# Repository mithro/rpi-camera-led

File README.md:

# RPi Camera LED

An interposer for the Raspberry Pi camera flex cable (15 pin, 1.0 mm pitch FPC).
It connects the Pi and camera, passes the camera bus through, and adds a
CH32V003A4M6 for I2C-controlled GPIO 11/12, PWM illumination LEDs, and ambient
light sensing. GPIO 11/12 use 10 kOhm couplers so the MCU can sense Pi-side
levels or drive the camera-side signals.

## Hardware

[KiCad schematic](hardware/rpi-camera-led.kicad_sch) ·
[PDF](hardware/rpi-camera-led.pdf) ·
[board](hardware/rpi-camera-led.kicad_pcb)

### Board: 15-way FFC camera interposer

| 3D render, top | 3D render, bottom | Layout (copper, silk, outline) |
|:--------------:|:-----------------:|:------------------------------:|
|  |  |  |

The routed interposer is 46.0 × 43.0 mm, two layers, with components on both
sides. J1 faces the Raspberry Pi and J2 faces the camera; they are opposite
edge-mounted so the two cable segments leave in line. The 11 mm lens aperture
is centered on the intended camera optical axis, and the illumination LEDs sit
around the aperture on the target-facing side. A fit-check using the supplied
Raspberry Pi Camera v3 3MF model guided the redesign: the 11 mm lens aperture
is aligned to the model's optical axis, and the four interposer holes now
match its 20.0 × 12.5 mm mounting pattern. The model's hole-pattern center is
offset 6.25 mm from the optical axis, so the holes are intentionally
asymmetric about the aperture. The LED row was moved clear of the relocated
mounting holes.

The four 2.2 mm mounting holes follow the supplied Raspberry Pi Camera v3
3MF mesh; see [hardware/cad/README.md](hardware/cad/README.md) for the model
datum and conversion details. The wider outline clears the connectors while
allowing the interposer to mount over the camera; the 6.05 mm-radius two-layer
copper keepout around the lens opening preserves copper-to-aperture edge
clearance. `check_pcb.py` asserts connector alignment and the camera-model
hole coordinates, pitch, and drill.
The 4-pin Qwiic/JST-SH connector (J3) is also edge-facing, with its cable entry
at the lower board edge (J3 at x=17.5 mm, y=53.7 mm, rotated 180°) so the plug
can be inserted without obstructing the camera or its flex. `check_pcb.py`
asserts this edge orientation and the J3 pad map as well as the FFC alignment.

**Routing and design checks pass:** KiCad DRC reports zero violations and
zero unconnected items, schematic ERC is clean, and the netlist matches the
design checker. The three camera differential pairs have these PCB-track
lengths (pads/connectors excluded):

| Pair | P length | N length | Intra-pair mismatch |
|---|---:|---:|---:|
| CSI data 0 | 35.5720 mm | 35.0432 mm | 0.5288 mm |
| CSI data 1 | 35.8428 mm | 35.3092 mm | 0.5336 mm |
| CSI clock | 36.9758 mm | 38.2571 mm | 1.2813 mm |

The data-pair averages are 2.3089 mm and 2.0405 mm shorter than the clock-pair
average. At a rough FR-4 propagation estimate of 6–7 ps/mm, those differences
correspond to about 12–16 ps; this is not a MIPI compliance claim. The actual
stackup/impedance and camera/host timing budget have not been verified.
Confirm the chosen fabricator's stackup and electrical rules before calling
the interposer signal-integrity qualified.

The Gerber/drill, position, sourced BOM and DRC archive is generated by
`uv run hardware/tools/export_manufacturing.py` into
`tmp/manufacturing/manufacturing.zip`. Export is blocked by any DRC errors or
unconnected items. The package is complete for review; verify vendor-specific
rules, current component availability, and the physical camera/FFC fit before
ordering. Production board identity/revision and license/attribution silkscreen
still need to be added and audited.

The camera/interposer stack model and test-render instructions are in
[hardware/cad/README.md](hardware/cad/README.md). The supplied camera model is
included as a faceted STEP converted from its 3MF source; the Raspberry Pi FFC
path remains illustrative.

| Populated interposer | Camera/interposer stackup concept |
|:--------------------:|:---------------------------------:|
|  |  |

The fit-check image shows the routed board with the supplied model's optical
axis and all four mounting holes aligned. This is a model-based fit check, not
physical verification; confirm the camera revision and mounting dimensions
before fabrication.

### How the cables run

| With cables fitted | Isometric |
|:------------------:|:---------:|
|  |  |

Both cables enter from the **outside** edges and run away from the board in
opposite directions, so the interposer drops into an existing cable run in
line. That follows from where the cable entry is on this connector: the
manufacturer's Section A‑A shows the solder tail stepping down and out at one
end while the cable channel opens at the other, and the top view labels
*Terminal* at one end and *Latch* at the other with the 5.30 mm housing
between them. It is also the only way a slide lock can work — you pull the
slider, insert the cable and push it back, all at the same end. So the cable
entry is at the latch end, away from the pads, and with each connector's
housing flush against its board edge that entry points outward.

The two cable stubs are drawn different ways up, and that is the point. J1 is
bottom contact, so its cable presents bared copper *downwards* and shows you
the blue backing; J2 is top contact, so its cable is the other way up and
shows you the conductors. That flip is the whole reason for pairing an F part
with an E part, and it is what lets both segments be ordinary Raspberry Pi
camera cables — the same flip you can see in a real cable, blue stiffener on
one face at one end, bared conductors on the other face at the other.

The stubs are illustrative and are not part of the board: they exist only in a
throwaway copy that the render script builds and deletes. Their 16.00 × 0.30 mm
section is the drawing's recommended FFC dimension. The bared conductors and
the backing are drawn a little longer than the 4 mm insertion depth so that a
few millimetres of each stay visible outside the connector — otherwise the
orientation they exist to show would be buried inside it.

Regenerate the images with `uv run hardware/tools/render_board.py`, and the
connector models with `uv run hardware/tools/gen_connector_model.py`. The
render script refills the copper zones first, via the pcbnew Python module
inside the KiCad snap, because `kicad-cli` has no zone-fill command and a
stale pour renders as authoritatively as a fresh one — when this was first
wired up the stored B.Cu pour was less than half its true area, and refilling
it dropped DRC from 116 violations to 17.

### Connectors, and which cables fit

J1 and J2 are **not** the same part, and that is deliberate:

| | part | contacts | mates with |
|---|---|---|---|
| **J1** → Raspberry Pi | JUSHUO AFA07-S15**F**CA-00 (LCSC C262721) | **bottom** — cable copper faces the board | a standard Pi camera cable |
| **J2** → camera | JUSHUO AFA07-S15**E**CA-00 (LCSC C262742) | **top** — cable copper faces away | a standard Pi camera cable |

The reason is cable parity. A Raspberry Pi camera cable is an *opposite-side*
FFC — "type 2", contacts on one face at one end and the other face at the other
— because the Pi's CSI socket is top-contact and the camera module's is
bottom-contact. Cutting one continuous cable anywhere yields one same-side half
and one opposite-side half, so an interposer whose two connectors want the
copper on the *same* face forces one odd, hard-to-buy cable. One that wants it
on *opposite* faces absorbs the asymmetry, and both segments become ordinary
Raspberry Pi camera cables. Bottom-contact at J1 plus top-contact at J2 is that
pairing.

The two variants share one land pattern — verified against both JUSHUO drawings
— so nothing on the board moves between them. Since only the contact side
differs, and it is invisible on an assembled board, the distinction is called
out in each symbol's value, in the MPN, and as a `BOTTOM CONTACT` / `TOP
CONTACT` marker on the fab layer.

Both footprints and their 3D models live in this repository, in
`hardware/rpi-camera-led.pretty` and `hardware/rpi-camera-led.3dshapes`. KiCad's
stock footprint references a STEP file for the JUSHUO AFA07 series that does not
exist — not in the KiCad distribution and not in `kicad-packages3D` upstream,
which ships no JUSHUO models at all. Third-party libraries have one, but under
terms that forbid redistribution, so `hardware/tools/gen_connector_model.py`
builds it from the manufacturer's published drawing instead: a 22.00 × 6.95 ×
2.50 mm envelope matching the drawing's DIM D, the F.Fab outline and the side
view's height, with the housing and latch coloured as the drawing's notes
specify. Both STEP and WRL are generated, the latter in the 0.1-inch units
KiCad expects.

The direct pass-through signals are wired J1 pin *k* ↔ J2 pin *16−k*. That
looks reversed but is exactly right: the two connectors are 180° apart, so J1
pad *k* physically faces J2 pad *16−k*. Camera GPIO 11/12 are the exception:
their Pi-side and camera-side nets are coupled through R6/R7 (10 kOhm) so U1
can sense the Pi and override the camera-side level. `check_pcb.py` measures
connector alignment as a number, because losing it to a stray drag puts a
dogleg in the direct pass-through nets and is invisible by eye.

### Verifying

```
uv run hardware/tools/check_schematic.py   # ERC + netlist vs design intent
uv run hardware/tools/check_pcb.py         # connector alignment + DRC parity
```

`check_schematic.py` checks ERC and expected connectivity. The final design
uses the CH32V003A4M6 SOP-16 pin map; firmware build verification is documented
in [firmware/README.md](firmware/README.md). Hardware bring-up has not yet
been performed.

## Firmware

[CH32V003 firmware](firmware/README.md): a fail-safe I2C bootloader plus an
application exposing camera GPIO control, RPi-side GPIO readback, GPIO
pass-through, LED brightness (hardware PWM) and an ambient light reading over
a Linux-friendly SMBus register map at address 0x42. Builds with
`riscv64-unknown-elf-gcc` and [ch32v003fun](https://github.com/cnlohr/ch32v003fun)
(`git submodule update --init`, then `make` in `firmware/bootloader` and
`firmware/app`).

The firmware pin map matches the current schematic and both bootloader and
application build with the documented open-source RISC-V toolchain. The
firmware has not been flashed or tested on physical hardware.

## Research

Part availability research comparing [JLCPCB's PCBA parts
library](https://jlcpcb.com/parts) and [NextPCB's Rev0
service](https://www.nextpcb.com/rev0-pcba) (which sources components from [HQ
Online](https://www.hqonline.com/)'s 600k+ in-stock inventory):

* [I2C controllable RGB LEDs](research/i2c-rgb-leds.md)
* [I2C GPIO expanders with LED driving capability](research/i2c-gpio-expanders.md)
* [Cheap (< $0.50) MCUs with I2C and no external parts required](research/cheap-mcus.md)
* [RPi camera compatible FPC connectors (1.0 mm pitch, 15 pin)](research/fpc-connectors.md)

## License

Apache 2.0 — see [LICENSE](LICENSE).

## Manufacturing outputs

Run `uv run hardware/tools/export_manufacturing.py` to write Gerbers, drill
files, positions, sourced/JLCPCB BOMs and `manufacturing.zip` into
`tmp/manufacturing/`. It checks DRC before export and reports parts missing an
LCSC number; the current design passes DRC and the BOM has no missing LCSC
codes. `--allow-incomplete` permits a review-only export and labels it
`NOT_FOR_FABRICATION.txt`—never send that package to a board house.
`kicad-cli` is found automatically; set `KICAD_CLI` to override. See issue #1
for the remaining production qualification work.

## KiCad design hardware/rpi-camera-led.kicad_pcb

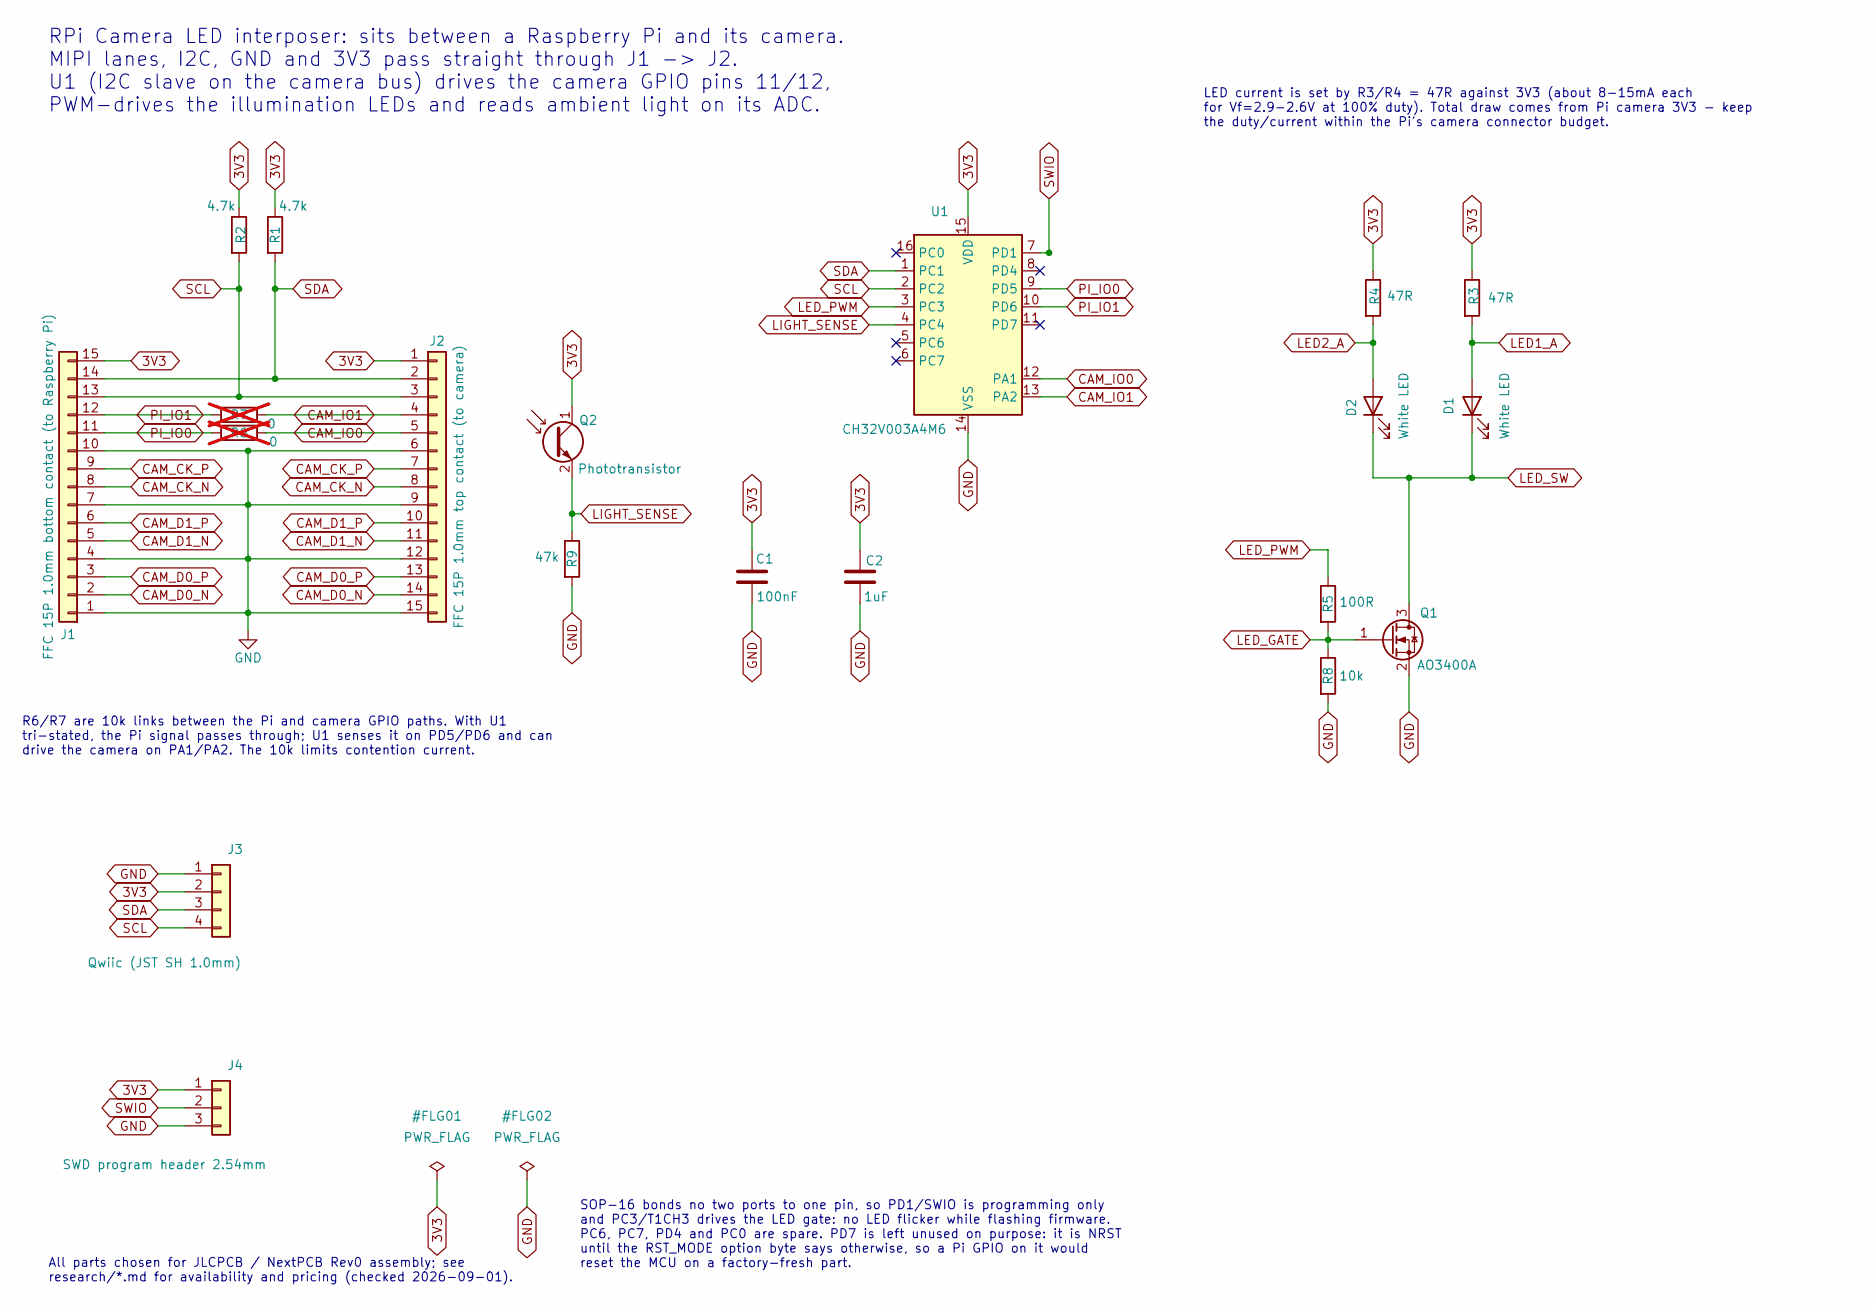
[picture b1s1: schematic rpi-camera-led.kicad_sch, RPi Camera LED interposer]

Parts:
C1: 100nF; C_0402_1005Metric; MPN GRM155R71A104KA01D; LCSC C71687
C2: 1uF; C_0402_1005Metric; MPN GRM155R61A105KE15D; LCSC C105172
D1, D2: White LED; LED_0805_2012Metric; MPN NCD0805W1; LCSC C110099
J1: FFC 15P 1.0mm bottom contact (to Raspberry Pi); JUSHUO_AFA07-S15FCA-00_1x15-1MP_P1.0mm_Horizontal; MPN AFA07-S15FCA-00; LCSC C262721
J2: FFC 15P 1.0mm top contact (to camera); JUSHUO_AFA07-S15ECA-00_1x15-1MP_P1.0mm_Horizontal; MPN AFA07-S15ECA-00; LCSC C262742
J3: Qwiic (JST SH 1.0mm); JST_SH_SM04B-SRSS-TB_1x04-1MP_P1.00mm_Horizontal; MPN SM04B-SRSS-TB; LCSC C160404
J4: SWD program header 2.54mm; PinHeader_1x03_P2.54mm_Vertical; MPN PBC03SAAN; LCSC C3333754
Q1: AO3400A; SOT-23; MPN AO3400A; LCSC C20917
Q2: Phototransistor; LED_0805_2012Metric; MPN TEMT7000X01; LCSC C499538
R1, R2: 4.7k; R_0402_1005Metric; MPN RC0402FR-074K7L; LCSC C105871
R3, R4: 47R; R_0603_1608Metric; MPN RC0603FR-0747RL; LCSC C114623
R5: 100R; R_0402_1005Metric; MPN RC0402FR-07100RL; LCSC C106232
R6, R7: 0; R_0402_1005Metric; not fitted
R8: 10k; R_0402_1005Metric; MPN RC0402FR-0710KL; LCSC C137965
R9: 47k; R_0402_1005Metric; MPN RC0402FR-0747KL; LCSC C93943
U1: CH32V003A4M6; SOIC-16_3.9x9.9mm_P1.27mm; MPN CH32V003A4M6; LCSC C5346357

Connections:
3V3: C1.1, C2.1, J1.15, J2.1, J3.2, J4.1, Q2.1 (C), R1.1, R2.1, R3.1, R4.1, U1.15 (VDD)
CAM_CK_N: J1.8, J2.8
CAM_CK_P: J1.9, J2.7
CAM_D0_N: J1.2, J2.14
CAM_D0_P: J1.3, J2.13
CAM_D1_N: J1.5, J2.11
CAM_D1_P: J1.6, J2.10
CAM_IO0: J2.5, R6.2, U1.12 (PA1)
CAM_IO1: J2.4, R7.2, U1.13 (PA2)
GND: C1.2, C2.2, J1.1, J1.4, J1.7, J1.10, J2.6, J2.9, J2.12, J2.15, J3.1, J4.3, Q1.2 (S), R8.2, R9.2, U1.14 (VSS)
LED1_A: D1.2 (A), R3.2
LED2_A: D2.2 (A), R4.2
LED_GATE: Q1.1 (G), R5.2, R8.1
LED_PWM: R5.1, U1.3 (PC3)
LED_SW: D1.1 (K), D2.1 (K), Q1.3 (D)
LIGHT_SENSE: Q2.2 (E), R9.1, U1.4 (PC4)
PI_IO0: J1.11, R6.1, U1.9 (PD5)
PI_IO1: J1.12, R7.1, U1.10 (PD6)
SCL: J1.13, J2.3, J3.4, R2.2, U1.2 (PC2)
SDA: J1.14, J2.2, J3.3, R1.2, U1.1 (PC1)
SWIO: J4.2, U1.7 (PD1)

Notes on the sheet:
All parts chosen for JLCPCB / NextPCB Rev0 assembly; see research/*.md for availability and pricing (checked 2026-09-01).
RPi Camera LED interposer: sits between a Raspberry Pi and its camera. MIPI lanes, I2C, GND and 3V3 pass straight through J1 -> J2. U1 (I2C slave on the camera bus) drives the camera GPIO pins 11/12, PWM-drives the illumination LEDs and reads ambient light on its ADC.
R6/R7 are 10k links between the Pi and camera GPIO paths. With U1 tri-stated, the Pi signal passes through; U1 senses it on PD5/PD6 and can drive the camera on PA1/PA2. The 10k limits contention current.
LED current is set by R3/R4 = 47R against 3V3 (about 8-15mA each for Vf=2.9-2.6V at 100% duty). Total draw comes from Pi camera 3V3 - keep the duty/current within the Pi's camera connector budget.
SOP-16 bonds no two ports to one pin, so PD1/SWIO is programming only and PC3/T1CH3 drives the LED gate: no LED flicker while flashing firmware. PC6, PC7, PD4 and PC0 are spare. PD7 is left unused on purpose: it is NRST until the RST_MODE option byte says otherwise, so a Pi GPIO on it would reset t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

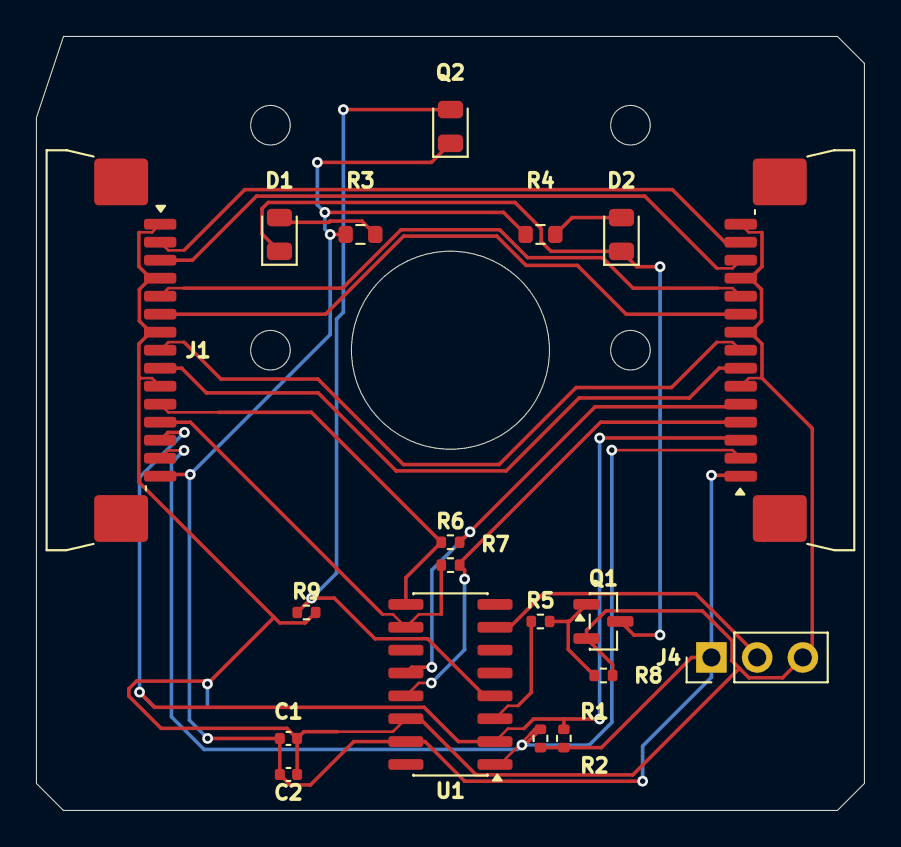
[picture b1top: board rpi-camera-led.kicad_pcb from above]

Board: 2 copper layers, 46.0 x 43.0 mm, 24 parts (1 on the bottom side), 21 nets.

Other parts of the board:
H1, H2, H3, H4: MountingHole_2.2mm_M2

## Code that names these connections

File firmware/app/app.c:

/*
 * CH32V003A4M6 camera-LED controller -- application.
 *
 * See firmware/README.md for the full pin map and register map. Short
 * version:
 *
 *   PD5 / PD6            -> Pi-side GPIO0/GPIO1 input sense
 *   PA1 / PA2            -> camera-side GPIO0/GPIO1 drive or high-Z
 *   PC1/PC2               -> I2C1 SDA/SCL (slave, address I2C_SLAVE_ADDR)
 *   PC4                   -> ADC1 channel A2, phototransistor light sensor
 *   PC3                   -> TIM1 CH3 hardware PWM, white LED gate
 */

#include "ch32fun.h"
#include <stdint.h>
#include <stdbool.h>
#include <string.h>

#include "../common/layout.h"
#include "../common/regmap_app.h"
#include "../common/i2c_slave.h"

/* Same cross-reset handshake word as the bootloader -- see
 * bootloader/bootloader.c and app.ld's .noinit section. */
volatile uint32_t noinit_boot_flag __attribute__((section(".noinit")));

static volatile uint8_t regs[REG_APP_SIZE];
static volatile bool boot_requested = false;

/* ---------------------------------------------------------------- */
/* I2C register file glue                                            */
/* ---------------------------------------------------------------- */

static void onWrite(uint8_t reg, uint8_t length)
{
	if (reg <= REG_BOOT && (uint16_t)reg + length > REG_BOOT) {
		if (regs[REG_BOOT] == REG_BOOT_MAGIC)
			boot_requested = true;
		regs[REG_BOOT] = 0;
	}
}

/* ---------------------------------------------------------------- */
/* GPIO passthrough: PD5/PD6 sense Pi; PA1/PA2 drive camera side.   */
/* ---------------------------------------------------------------- */

static void update_gpio_channel(uint32_t pi_pin, uint32_t camera_pin, uint8_t bit)
{
	bool copy_en = regs[REG_CTRL] & bit;
	bool oe = regs[REG_GPIO_OE] & bit;
	bool out_level = regs[REG_GPIO_OUT] & bit;

	funPinMode(pi_pin, GPIO_CFGLR_IN_FLOAT);
	if (copy_en || !oe) {
		funPinMode(camera_pin, GPIO_CFGLR_IN_FLOAT);
	} else {
		/* Load OUTDR *before* enabling the output driver. OUTDR
		 * keeps whatever was last written to it (0 out of reset),
		 * so configuring the pin as a push-pull output first would
		 * drive the stale level onto the camera's GPIO for the few
		 * cycles until funDigitalWrite() caught up -- a real glitch
		 * on every 0->1 transition of GPIO_OE. Writing OUTDR while
		 * the pin is still a floating input has no effect on the
		 * pin (OUTDR only selects the pull direction in the
		 * pull-up/pull-down input modes, which this is not). */
		funDigitalWrite(camera_pin, out_level ? FUN_HIGH : FUN_LOW);
		funPinMode(camera_pin, GPIO_CFGLR_OUT_10Mhz_PP);
	}

	/* Live pin read: reflects the Pi's passed-through state when
	 * tri-stated (copy mode or OE=0), or the value we're driving
	 * when OE=1 and copy mode is off -- see README.md. */
	if (funDigitalRead(pi_pin))
		regs[REG_GPIO_IN] |= bit;
	else
		regs[REG_GPIO_IN] &= ~bit;
}

/* ---------------------------------------------------------------- */
/* ADC (PC4 / ANALOG_2), continuously sampled + averaged              */
/* ---------------------------------------------------------------- */

/* SysTick does NOT run at the core clock by default: ch32fun's
 * handle_reset() writes SysTick->CTLR = 1 (HCLK/8) unless
 * FUNCONF_SYSTICK_USE_HCLK is set, in which case it writes 5 (HCLK).
 * See the "SYSTICK info" block in ch32fun.h. Derive the tick rate
 * instead of assuming it equals FUNCONF_SYSTEM_CORE_CLOCK, or the
 * sample period silently comes out 8x too long. */
#if defined(FUNCONF_SYSTICK_USE_HCLK) && FUNCONF_SYSTICK_USE_HCLK
#define SYSTICK_HZ (FUNCONF_SYSTEM_CORE_CLOCK)
#else
#define SYSTICK_HZ (FUNCONF_SYSTEM_CORE_CLOCK / 8u)
#endif

#define LIGHT_SAMPLE_HZ 100u
#define LIGHT_SAMPLE_PERIOD_TICKS (SYSTICK_HZ / LIGHT_SAMPLE_HZ)
#define LIGHT_EMA_SHIFT 3 /* averages over 2^3 = 8 samples */

static void adc_init(void)
{
	RCC->CFGR0 &= ~(0x1Fu << 11); /* ADCCLK = HCLK/2 */
	RCC->APB2PCENR |= RCC_APB2Periph_ADC1;

	RCC->APB2PRSTR |= RCC_APB2Periph_ADC1;
	RCC->APB2PRSTR &= ~RCC_APB2Periph_ADC1;

	funPinMode(PC4, GPIO_CFGLR_IN_ANALOG);

	ADC1->RSQR1 = 0;
	ADC1->RSQR2 = 0;
	ADC1->RSQR3 = ANALOG_2;

	ADC1->SAMPTR2 &= ~(ADC_SMP0 << (3 * ANALOG_2));
	ADC1->SAMPTR2 |= (uint32_t)7 << (3 * ANALOG_2); /* longest sample time */

	ADC1->CTLR2 |= ADC_ADON | ADC_EXTSEL;

	ADC1->CTLR2 |= CTLR2_RSTCAL_Set;
	while (ADC1->CTLR2 & CTLR2_RSTCAL_Set)
		;
	ADC1->CTLR2 |= CTLR2_CAL_Set;
	while (ADC1->CTLR2 & CTLR2_CAL_Set)
		;
}

static uint16_t adc_sample(void)
{
	ADC1->CTLR2 |= ADC_SWSTART;
	while (!(ADC1->STATR & ADC_EOC))
		;
	return (uint16_t)ADC1->RDATAR;
}

static void light_poll(void)
{
	static uint32_t last_tick;
	/* Accumulator held scaled by 2^LIGHT_EMA_SHIFT. Doing the average
	 * as `ema += (sample - ema) >> SHIFT` on an unscaled value instead
	 * loses the low bits of every update, so the filter stalls short
	 * of its input (a steady 1023 settles at ~1016 and full scale is
	 * never reachable). */
	static int32_t acc;
	static bool primed = false;

	uint32_t now = funSysTick32();
	if (primed && (now - last_tick) < LIGHT_SAMPLE_PERIOD_TICKS)
		return;
	last_tick = now;

	int32_t sample = adc_sample();
	if (!primed) {
		acc = sample << LIGHT_EMA_SHIFT; /* start at the first reading */
		primed = true;
	} else {
		acc += sample - (acc >> LIGHT_EMA_SHIFT);
	}

	uint16_t v = (uint16_t)(acc >> LIGHT_EMA_SHIFT);
	/* Publish both halves atomically with respect to the I2C
	 * interrupt, so a host reading LIGHT_LO..LIGHT_HI in one burst
	 * can never get the low byte of one sample and the high byte of
	 * the next. */
	__disable_irq();
	regs[REG_LIGHT_LO] = (uint8_t)(v & 0xFF);
	regs[REG_LIGHT_HI] = (uint8_t)(v >> 8);
	__enable_irq();
}

/* ---------------------------------------------------------------- */
/* LED PWM (PC3 = TIM1 CH3, NOREMAP mapping)                         */
/* ---------------------------------------------------------------- */

/* PSC=186 (divide by 187) with ATRLR=255 (256 counts) gives
 * 48MHz / 187 / 256 =~ 1.003kHz PWM, and lets an 8-bit brightness
 * value map 1:1 onto the compare register. */
#define LED_PWM_PSC   186
#define LED_PWM_ATRLR 255

static void led_pwm_init(void)
{
	RCC->APB2PCENR |= RCC_APB2Periph_TIM1 | RCC_APB2Periph_AFIO;

	RCC->APB2PRSTR |= RCC_APB2Periph_TIM1;
	RCC->APB2PRSTR &= ~RCC_APB2Periph_TIM1;

	TIM1->CTLR1 = TIM_ARPE; /* buffer ATRLR too */
	TIM1->CTLR2 = 0;
	TIM1->PSC = LED_PWM_PSC;
	TIM1->ATRLR = LED_PWM_ATRLR;

	/* PWM mode 1 (OC3M = 110) with the compare value preloaded, so a
	 * brightness change is applied at an update event rather than
	 * mid-period. */
	TIM1->CHCTLR2 |= TIM_OC3M_2 | TIM_OC3M_1 | TIM_OC3PE;

	TIM1->CCER &= ~(TIM_CC3P | TIM_CC3NE | TIM_CC3NP);
	TIM1->CCER |= TIM_CC3E;

	TIM1->CH3CVR = 0;
	TIM1->SWEVGR |= TIM_UG; /* load PSC/ATRLR/CH3CVR preloads */

	TIM1->BDTR |= TIM_MOE;
	TIM1->CTLR1 |= TIM_CEN;

	funPinMode(PC3, GPIO_CFGLR_OUT_10Mhz_AF_PP);
}

static void led_pwm_set(uint8_t brightness)
{
	/* ATRLR = 255 means the period is 256 counts, so a compare value
	 * of 255 is 255/256 = 99.6%, not fully on. Writing 256 (> ATRLR)
	 * holds OC3REF active for the entire period, which is what a
	 * brightness of 255 should mean. */
	TIM1->CH3CVR = (brightness == 255) ? 256 : brightness;
}

/* ---------------------------------------------------------------- */

int main(void)
{
	SystemInit();

	memset((void *)regs, 0, sizeof(regs));
	regs[REG_WHO_AM_I] = APP_WHO_AM_I_VALUE;
	regs[REG_FW_VERSION] = APP_FW_VERSION_VALUE;

	funGpioInitAll();

	funPinMode(PD5, GPIO_CFGLR_IN_FLOAT);
	funPinMode(PD6, GPIO_CFGLR_IN_FLOAT);

	/* CAM_IO0/CAM_IO1 start tri-stated (OE defaults to 0 in regs). */

	adc_init();
	led_pwm_init();

	funPinMode(PC1, GPIO_CFGLR_OUT_10Mhz_AF_OD); /* SDA */
	funPinMode(PC2, GPIO_CFGLR_OUT_10Mhz_AF_OD); /* SCL */
	SetupI2CSlave(I2C_SLAVE_ADDR, regs, sizeof(regs), onWrite, NULL, false);

	while (1) {
		/* The I2C slave driver has a single read_only flag for the
		 * whole register file, and this file must be writable
		 * (CTRL / GPIO_OUT / GPIO_OE / LED / BOOT), so a host can
		 * write the read-only registers too. Re-stamp the constant
		 * ones every pass; GPIO_IN and LIGHT are overwritten by
		 * their own producers below. */
		regs[REG_WHO_AM_I] = APP_WHO_AM_I_VALUE;
		regs[REG_FW_VERSION] = APP_FW_VERSION_VALUE;
		regs[REG_RESERVED_07] = 0;

		update_gpio_channel(PD5, PA1, GPIO_CH0);
		update_gpio_channel(PD6, PA2, GPIO_CH1);

		light_poll();

		led_pwm_set(regs[REG_LED]);

		if (boot_requested) {
			boot_requested = false;
			noinit_boot_flag = ENTER_BOOTLOADER_RAM_MAGIC;
			PFIC->SCTLR = 1u << 31; /* system reset; bootloader runs next */
			while (1)
				;
		}
	}
}
